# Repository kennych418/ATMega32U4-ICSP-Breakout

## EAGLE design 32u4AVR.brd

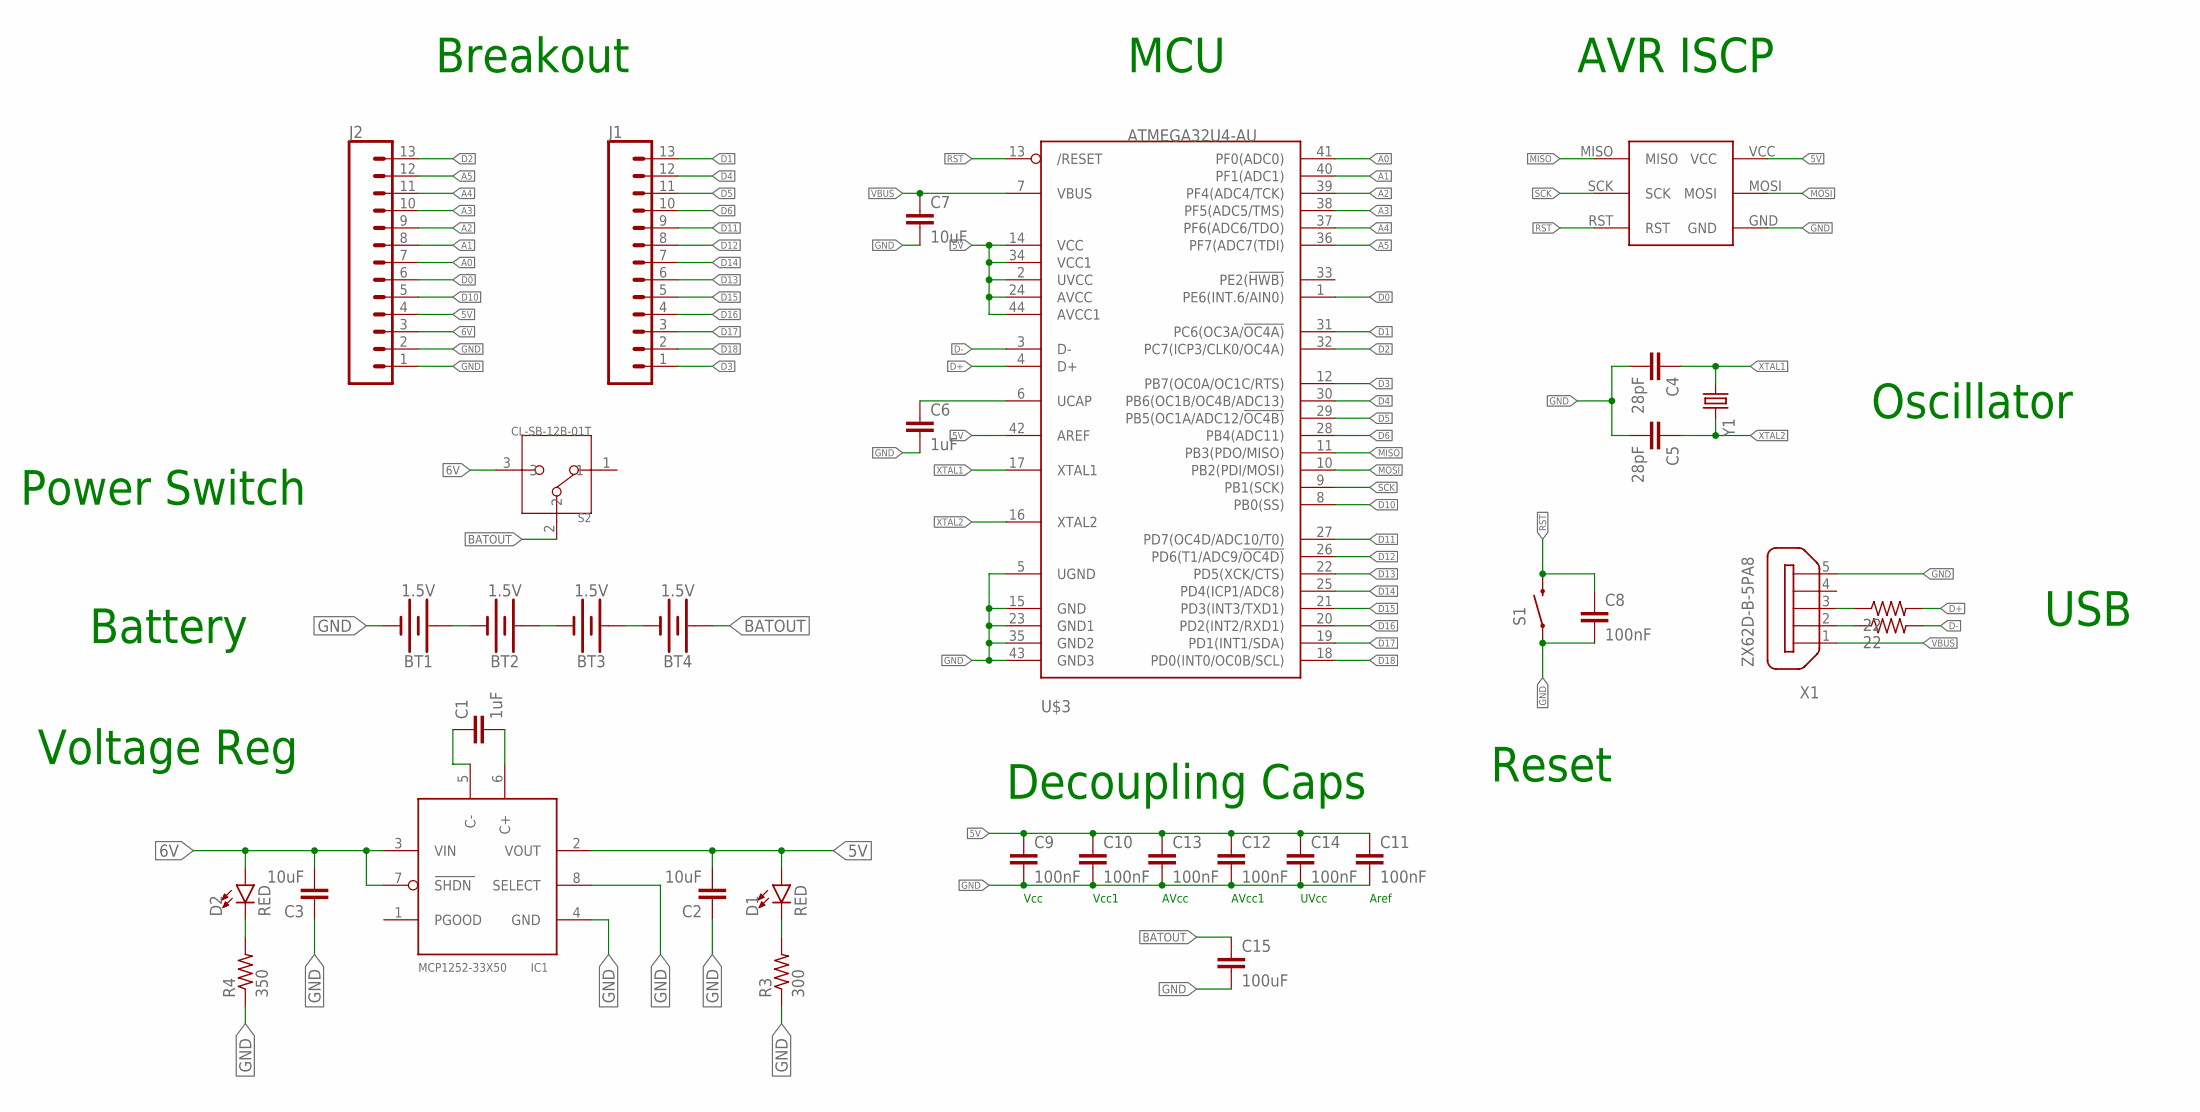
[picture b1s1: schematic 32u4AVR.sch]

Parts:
BT1, BT2, BT3, BT4: 1.5V; BATTERY-AA
C1, C6: 1uF; C0402K
C2, C3, C7: 10uF; C0402K
C4, C5: 28pF; C0402K
C8, C9, C10, C11, C12, C13, C14: 100nF; C0402K
C15: 100uF; C1206K
D1, D2: RED; LED-0603
IC1: MCP1252-33X50; MSOP8
J1, J2: CONN_13LONGPADS; 1X13-LONGPADS
R3: 300; R0402
R4: 350; R0402
R5, R6: 22; R0402
S1: SWITCH-MOMENTARY-2SMD; TACTILE-SWITCH-SMD
S2: CL-SB-12B-01T; CL-SB-12B
U$1: AVR-ISP
U$3: ATMEGA32U4-AU; TQFP44
X1: ZX62D-B-5PA8
Y1: CRYSTALSMD; HC49UP

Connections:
5V: C2.2, C9.1, C10.1, C11.1, C12.1, C13.1, C14.1, D1.A, IC1.2 (VOUT), J2.4, U$1.VCC, U$3.2 (UVCC), U$3.14 (VCC), U$3.24 (AVCC), U$3.34 (VCC1), U$3.42 (AREF), U$3.44 (AVCC1)
6V: C3.2, D2.A, IC1.3 (VIN), IC1.7 (SHDN), J2.3, S2.3
A0: J2.7, U$3.41 (PF0(ADC0))
A1: J2.8, U$3.40 (PF1(ADC1))
A2: J2.9, U$3.39 (PF4(ADC4/TCK))
A3: J2.10, U$3.38 (PF5(ADC5/TMS))
A4: J2.11, U$3.37 (PF6(ADC6/TDO))
A5: J2.12, U$3.36 (PF7(ADC7(TDI))
BATOUT: BT4.PWR@1 (+), C15.1, S2.2
D0: J2.6, U$3.1 (PE6(INT.6/AIN0))
D1: J1.13, U$3.31 (PC6(OC3A/!OC4A))
D2: J2.13, U$3.32 (PC7(ICP3/CLK0/OC4A))
D3: J1.1, U$3.12 (PB7(OC0A/OC1C/RTS))
D4: J1.12, U$3.30 (PB6(OC1B/OC4B/ADC13))
D5: J1.11, U$3.29 (PB5(OC1A/ADC12/!OC4B))
D6: J1.10, U$3.28 (PB4(ADC11))
D10: J2.5, U$3.8 (PB0(SS))
D11: J1.9, U$3.27 (PD7(OC4D/ADC10/T0))
D12: J1.8, U$3.26 (PD6(T1/ADC9/!OC4D))
D13: J1.6, U$3.22 (PD5(XCK/CTS))
D14: J1.7, U$3.25 (PD4(ICP1/ADC8))
D15: J1.5, U$3.21 (PD3(INT3/TXD1))
D16: J1.4, U$3.20 (PD2(INT2/RXD1))
D17: J1.3, U$3.19 (PD1(INT1/SDA))
D18: J1.2, U$3.18 (PD0(INT0/OC0B/SCL))
D+: R5.2, U$3.4 (D+)
D-: R6.2, U$3.3 (D-)
GND: BT1.GND@1 (-), C2.1, C3.1, C4.2, C5.2, C6.2, C7.2, C8.2, C9.2, C10.2, C11.2, C12.2, C13.2, C14.2, C15.2, IC1.4 (GND), IC1.8 (SELECT), J2.1, J2.2, R3.1, R4.1, S1.1, U$1.GND, U$3.5 (UGND), U$3.15 (GND), U$3.23 (GND1), U$3.35 (GND2), U$3.43 (GND3), X1.5
MISO: U$1.MISO, U$3.11 (PB3(PDO/MISO))
MOSI: U$1.MOSI, U$3.10 (PB2(PDI/MOSI))
unnamed: C1.1, IC1.5 (C-)
unnamed: C1.2, IC1.6 (C+)
unnamed: BT1.PWR@1 (+), BT2.GND@1 (-)
unnamed: BT2.PWR@1 (+), BT3.GND@1 (-)
unnamed: BT3.PWR@1 (+), BT4.GND@1 (-)
unnamed: R6.1, X1.2
unnamed: R5.1, X1.3
unnamed: C6.1, U$3.6 (UCAP)
unnamed: D1.C, R3.2
unnamed: D2.C, R4.2
RST: C8.1, S1.3 (2), U$1.RST, U$3.13 (/RESET)
SCK: U$1.SCK, U$3.9 (PB1(SCK))
VBUS: C7.1, U$3.7 (VBUS), X1.1
XTAL1: C4.1, U$3.17 (XTAL1), Y1.1
XTAL2: C5.1, U$3.16 (XTAL2), Y1.2

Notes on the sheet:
MCU
AVR ISCP
Breakout
Oscillator
USB
Reset
Battery
Voltage Reg
Decoupling Caps
Vcc
Vcc1
Aref
AVcc
AVcc1
UVcc
Power Switch

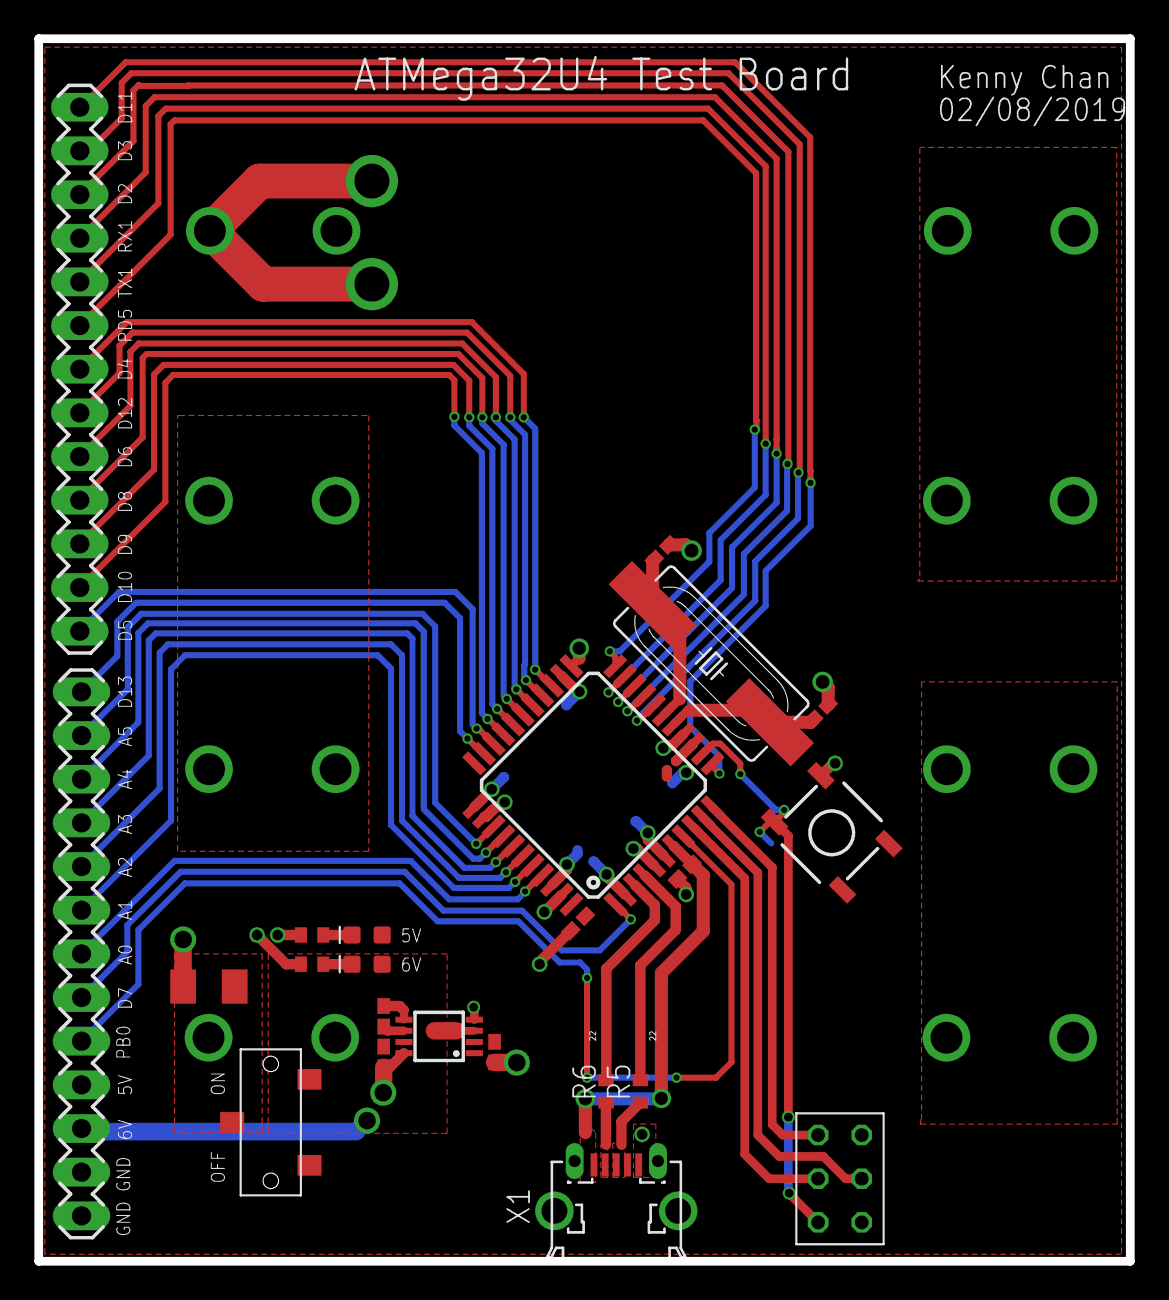
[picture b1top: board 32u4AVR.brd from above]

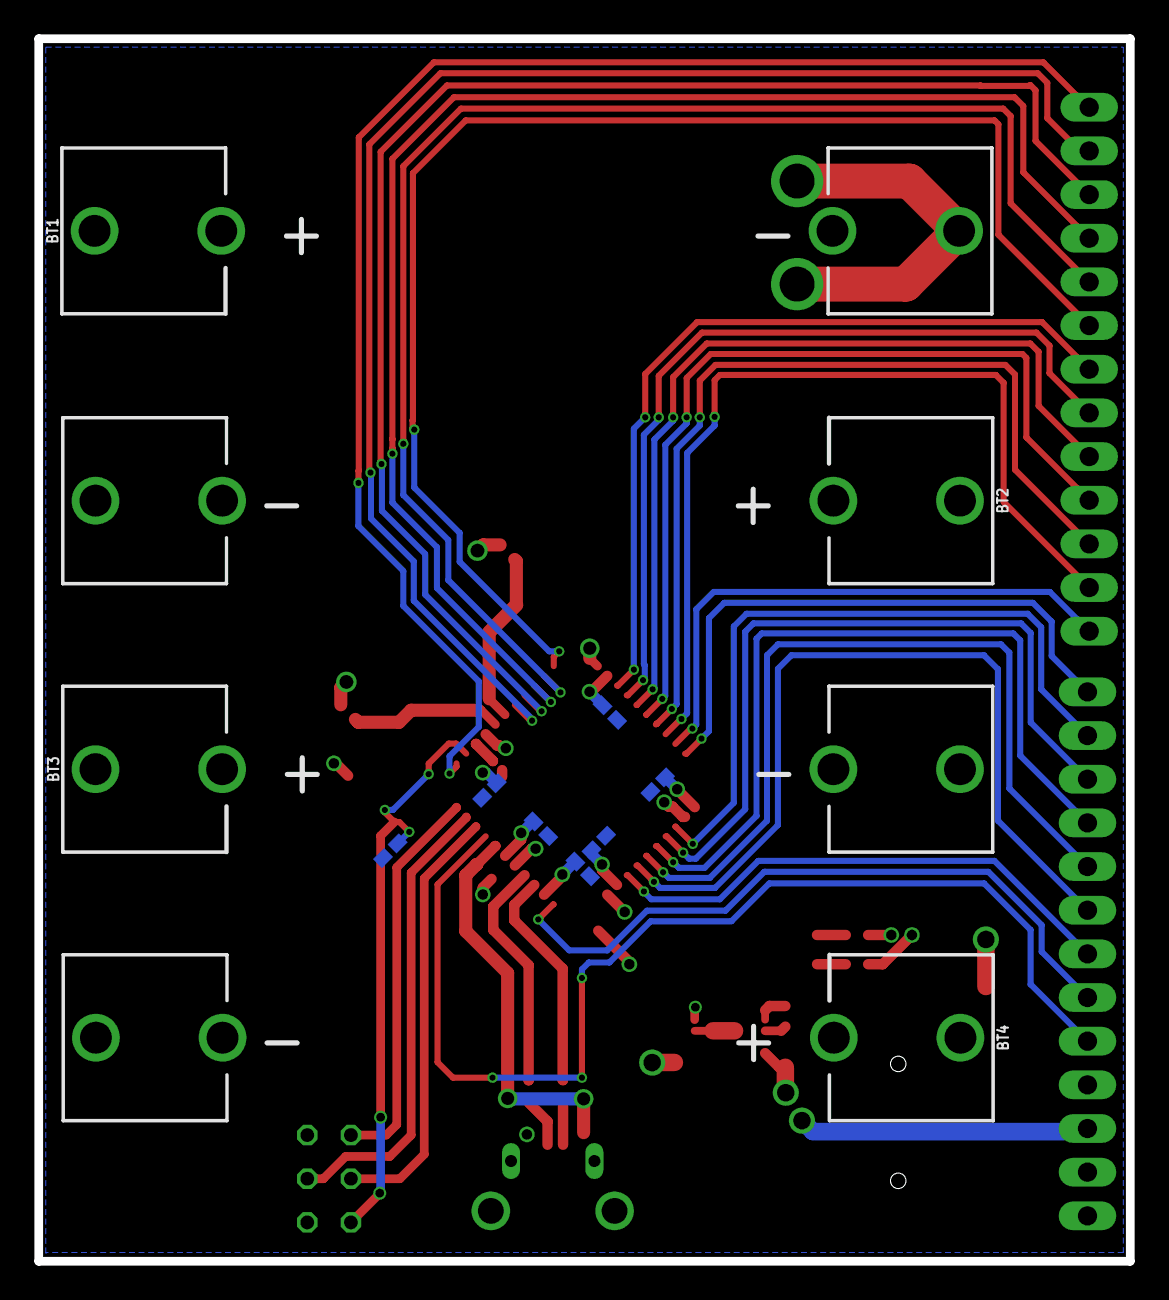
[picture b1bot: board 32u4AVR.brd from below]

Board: 2 copper layers, 63.5 x 71.1 mm, 34 parts (11 on the bottom side), 45 nets.

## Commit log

2019-02-11 Adding Schematic, PCB, and BOM
2019-08-23 Replaced USB A with micro USB

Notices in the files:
parts and their libraries:
SparkFun-Batteries: Licensing: Creative Commons ShareAlike 4.0 International - https://creativecommons.org/licenses/by-sa/4.0
